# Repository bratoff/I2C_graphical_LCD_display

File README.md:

I2C_graphical_LCD_display
=========================

Arduino library for KS0108 LCD displays using I2C, SPI or bit-bang serial protocol.

Forked from https://github.com/nickgammon/I2C_graphical_LCD_display

Enhanced by Bruce Ratoff, KO4XL@yahoo.com, https://github.com/bratoff

For details about the theory, wiring, schematic, etc. see:
http://www.gammon.com.au/forum/?id=10940

LCD display: KS0108
IO expander: MCP23017 (also supported is the SPI version of the chip: MCP23S17)

Library documentation also on the above web page.

The original library has been expanded to include open and filled circles, and
an additional interface has been added using two 74HC595 latched shift registers.

Other enhancements include:
- Significant speed improvement in WRITETHRU_CACHE mode
- Optimization of shape drawing algorithms
- Conditional compilations based on presence of I2C and/or SPI libraries to reduce code size
- Platform-specific optimizations for AVR, some ARM architectures and ESP8266

PCBs can be ordered from OshPark.com:  
Shift register (2 wire) version:  <https://oshpark.com/shared_projects/ggrOvewK>  
I2C/SPI version:  <https://oshpark.com/shared_projects/1TWaorN2>  

Versions 2.x and 3.x Enhanced by B.Ratoff  
Version 2.x - Add circle drawing  
Version 3.x - Add support for 74HC595 2-wire interface see code comments for circuit info  
Version 4.x - Eliminate need to include I2C and SPI libraries when 74HC595 is used

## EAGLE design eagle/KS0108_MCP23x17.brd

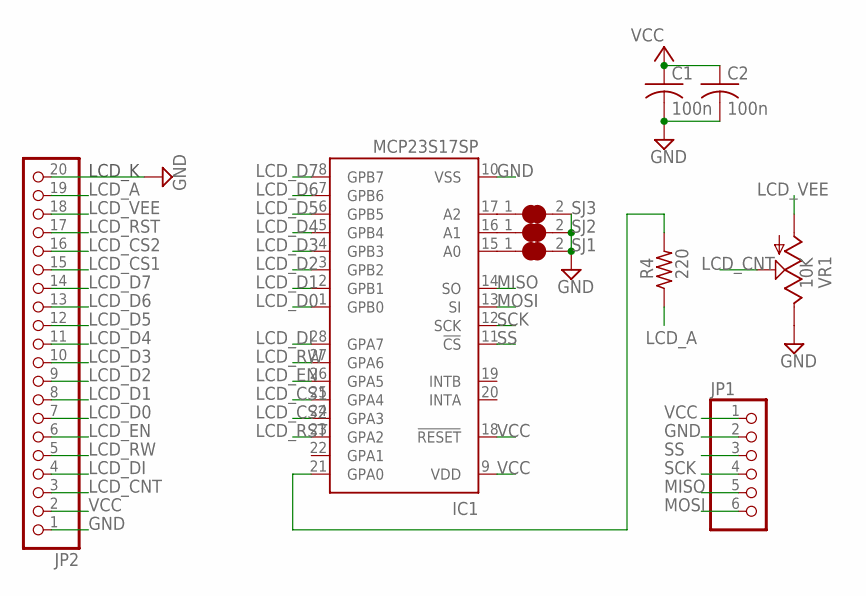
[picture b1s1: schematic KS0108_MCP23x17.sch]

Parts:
C1, C2: 100n; C0805K
IC1: MCP23S17SP; DIL28-3
JP1: PINHD-1X6CB; 1X06-CLEANBIG
JP2: PINHD-1X20-BIG; 1X20-BIG
R4: 220; R0805
SJ1, SJ2, SJ3: SOLDERJUMPER_CLOSED; SOLDERJUMPER_CLOSEDWIRE
VR1: 10K; B25P

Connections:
GND: C1.2, C2.2, IC1.10 (VSS), JP1.2, JP2.1, JP2.20, SJ1.2, SJ2.2, SJ3.2, VR1.E
LCD_A: JP2.19, R4.1
LCD_CNT: JP2.3, VR1.S
LCD_CS1: IC1.25 (GPA4), JP2.15
LCD_CS2: IC1.24 (GPA3), JP2.16
LCD_D0: IC1.1 (GPB0), JP2.7
LCD_D1: IC1.2 (GPB1), JP2.8
LCD_D2: IC1.3 (GPB2), JP2.9
LCD_D3: IC1.4 (GPB3), JP2.10
LCD_D4: IC1.5 (GPB4), JP2.11
LCD_D5: IC1.6 (GPB5), JP2.12
LCD_D6: IC1.7 (GPB6), JP2.13
LCD_D7: IC1.8 (GPB7), JP2.14
LCD_DI: IC1.28 (GPA7), JP2.4
LCD_EN: IC1.26 (GPA5), JP2.6
LCD_RST: IC1.23 (GPA2), JP2.17
LCD_RW: IC1.27 (GPA6), JP2.5
LCD_VEE: JP2.18, VR1.A
MISO: IC1.14 (SO), JP1.5
MOSI: IC1.13 (SI), JP1.6
unnamed: IC1.21 (GPA0), R4.2
unnamed: IC1.15 (A0), SJ1.1
unnamed: IC1.16 (A1), SJ2.1
unnamed: IC1.17 (A2), SJ3.1
SCK: IC1.12 (SCK), JP1.4
SS: IC1.11 (!CS), JP1.3
VCC: C1.1, C2.1, IC1.9 (VDD), IC1.18 (!RESET), JP1.1, JP2.2

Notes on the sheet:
LCD_K

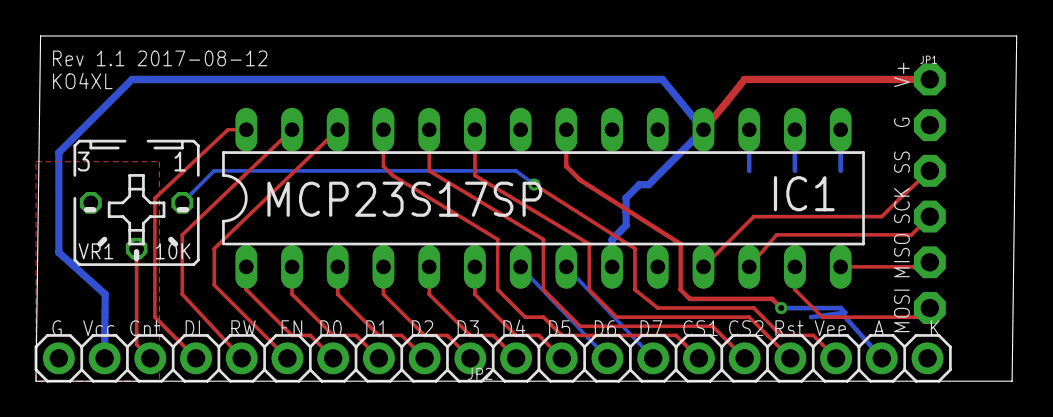
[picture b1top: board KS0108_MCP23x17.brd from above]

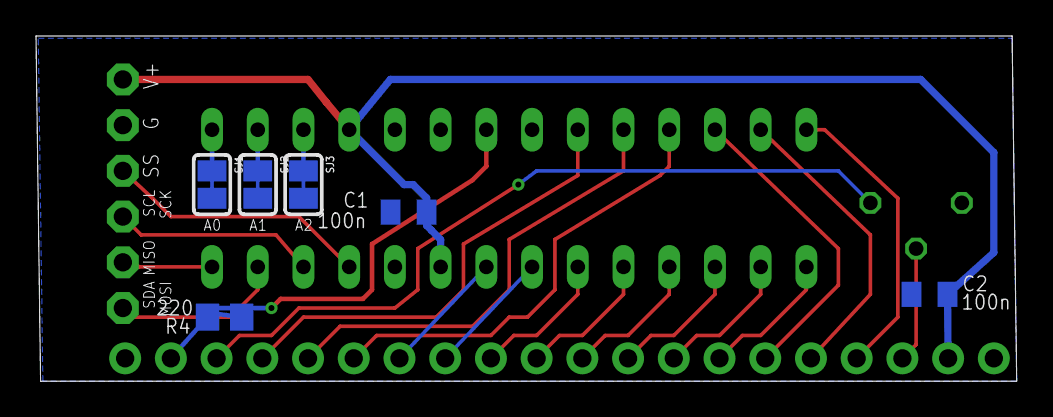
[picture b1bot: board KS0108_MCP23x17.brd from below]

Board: 2 copper layers, 54.5 x 19.2 mm, 10 parts (6 on the bottom side), 27 nets.

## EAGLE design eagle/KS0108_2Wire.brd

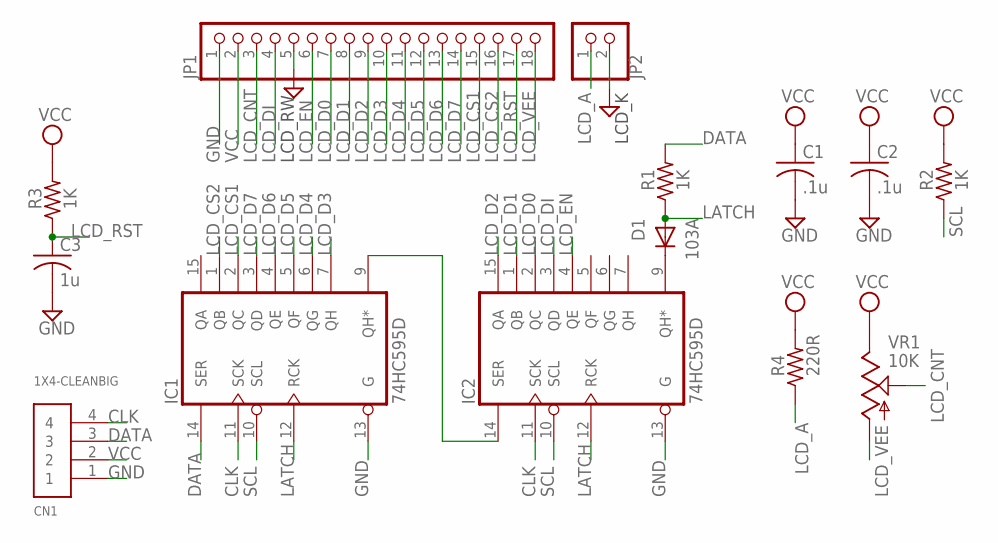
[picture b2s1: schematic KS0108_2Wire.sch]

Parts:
C1, C2: .1u; C1206
C3: 1u; C1206
CN1: 1X4-CLEANBIG; 1X04-CLEANBIG
D1: 103A; SOD80C
IC1, IC2: 74HC595D; SO16
JP1: PINHD-1X18-BIG; 1X18-BIG
JP2: HEADER-1X2ROUND; 1X02_ROUND
R1, R2, R3: 1K; R1206
R4: 220R; R1206
VR1: 10K; CT6

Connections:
CLK: CN1.4, IC1.11 (SCK), IC2.11 (SCK)
DATA: CN1.3, IC1.14 (SER), R1.2
GND: C1.2, C2.2, C3.2, CN1.1, IC1.8 (GND), IC1.13 (G), IC2.8 (GND), IC2.13 (G), JP1.1, JP1.5, JP2.2
LATCH: D1.A, IC1.12 (RCK), IC2.12 (RCK), R1.1
LCD_A: JP2.1, R4.1
LCD_CNT: JP1.3, VR1.S
LCD_CS1: IC1.2 (QC), JP1.15
LCD_CS2: IC1.1 (QB), JP1.16
LCD_D0: IC2.2 (QC), JP1.7
LCD_D1: IC2.1 (QB), JP1.8
LCD_D2: IC2.15 (QA), JP1.9
LCD_D3: IC1.7 (QH), JP1.10
LCD_D4: IC1.6 (QG), JP1.11
LCD_D5: IC1.5 (QF), JP1.12
LCD_D6: IC1.4 (QE), JP1.13
LCD_D7: IC1.3 (QD), JP1.14
LCD_DI: IC2.3 (QD), JP1.4
LCD_EN: IC2.4 (QE), JP1.6
LCD_RST: C3.1, JP1.17, R3.1
LCD_VEE: JP1.18, VR1.A
unnamed: IC1.9 (QH*), IC2.14 (SER)
unnamed: D1.C, IC2.9 (QH*)
SCL: IC1.10 (SCL), IC2.10 (SCL), R2.1
VCC: C1.1, C2.1, CN1.2, IC1.16 (VCC), IC2.16 (VCC), JP1.2, R2.2, R3.2, R4.2, VR1.E

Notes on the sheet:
LCD_RW
LCD_K

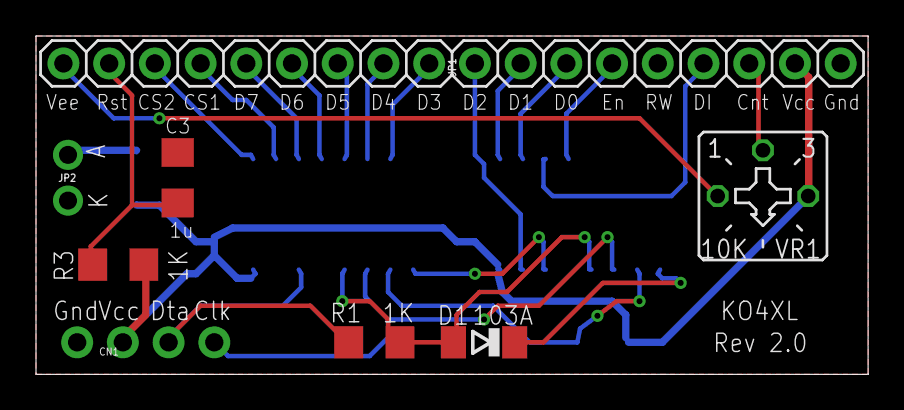
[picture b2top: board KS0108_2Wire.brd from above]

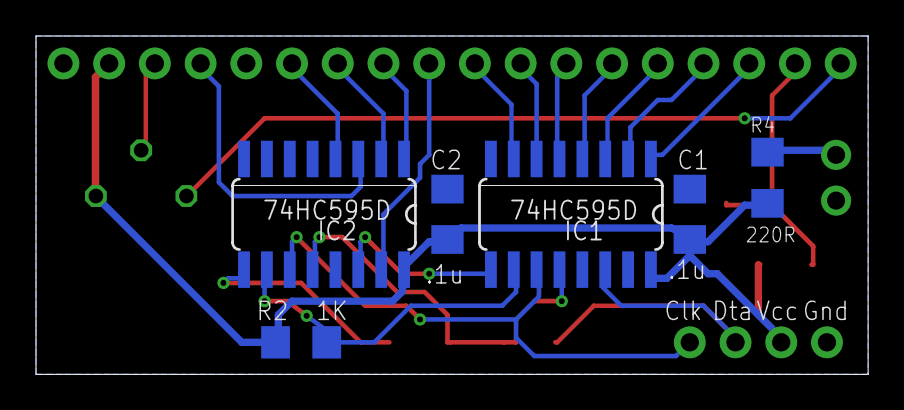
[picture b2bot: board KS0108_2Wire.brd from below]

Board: 2 copper layers, 46.2 x 18.8 mm, 14 parts (6 on the bottom side), 24 nets.

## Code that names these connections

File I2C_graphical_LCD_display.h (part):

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#define INTCAPB  0x11
#define GPIOA    0x12   // Port value. Write to change, read to obtain value
#define GPIOB    0x13
#define OLLATA   0x14   // Output latch. Write to latch output.
#define OLLATB   0x15


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  9   (QH*)        Carry   IC2 pin 14 (SER) IC1 shift register out to IC2 shift register in
 10   (SCL)        +5V     IC1 clear input pulled high (always disabled)
 11   (SCK)        CLK     Arduino output pin for CLK (NOTE: Same for IC1 and IC2)
 12   (RCK)        LATCH   IC2 pin 12 and anode of D1
 13   (G)          GND     IC1 output enable pulled low (always enabled)
 14   (SER)        DATA    Free side of R1 (see below) and Arduino output pin for DATA
 15   (QA)                 No connection
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  9   (QH*)        Control Cathode of D1
 10   (SCL)        +5V     IC2 clear input pulled high (always disabled)
 11   (SCK)        CLK     Arduino output pin for CLK (NOTE: Same for IC1 and IC2)
 12   (RCK)        LATCH   IC1 pin 12 and anode of D1 (NOTE: Same for IC1 and IC2)
 13   (G)          GND     IC2 output enable pulled low (always enabled - Same for IC1 and IC2)
 14   (SER)        Carry   IC1 pin 9 (QH*) IC2 shift register in from IC1 shift register out
 15   (QA)         D2      LCD pin 9
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																	D1 (cathode)
																	D1 (anode)
																	|
	DATA (from Arduino) o----R1-----o----o LATCH (to IC1 and IC2 pin 12)
													(1K)

LCD Power On Reset circuit:
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									|
									R3 (1K)
									|
									o----o LCD_RST (LCD pin 17)
									|
									C3 (1uf)
									|
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
// GPA port - these show which wires from the LCD are connected to which pins on the I/O expander

#define LCD_CS1    0b00000100   // chip select 1  (pin 23)                            0x04
#define LCD_CS2    0b00001000   // chip select 2  (pin 24)                            0x08
#define LCD_RESET  0b00010000   // reset (pin 25)                                     0x10
#define LCD_DATA   0b00100000   // 1xxxxxxx = data; 0xxxxxxx = instruction  (pin 26)  0x20
#define LCD_READ   0b01000000   // x1xxxxxx = read; x0xxxxxx = write  (pin 27)        0x40
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
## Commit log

2018-04-16 Initial commit
    Initial commit
2018-04-16 STM32F1 speedup
    Speed up STM32F1 using direct bit set/reset registers.
2018-04-18 Optimize for Teensy family
    Take advantage of M0 and M4 bit operations on Teensy boards
2018-04-18 SAMD optimization
    Detect and optimize for Arduino SAMD
2018-04-19 74HC595 eagle files
    Folder added containing Eagle CAD files for 74HC595 interface.
2020-05-15 Add MCP23x17
    Add Eagle board and schematic for MCP23x17 interface
2020-06-10 Version 4.1
    Cumulative update - refer to comments
2020-08-20 Add PDF schematics

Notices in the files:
parts and their libraries:
microbuilder: This work is placed in the public domain, and may be freely used for commercial and non-commercial work with the following conditions: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
